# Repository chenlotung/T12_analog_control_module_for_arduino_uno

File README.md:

# T12_analog_control_module_for_arduino_uno

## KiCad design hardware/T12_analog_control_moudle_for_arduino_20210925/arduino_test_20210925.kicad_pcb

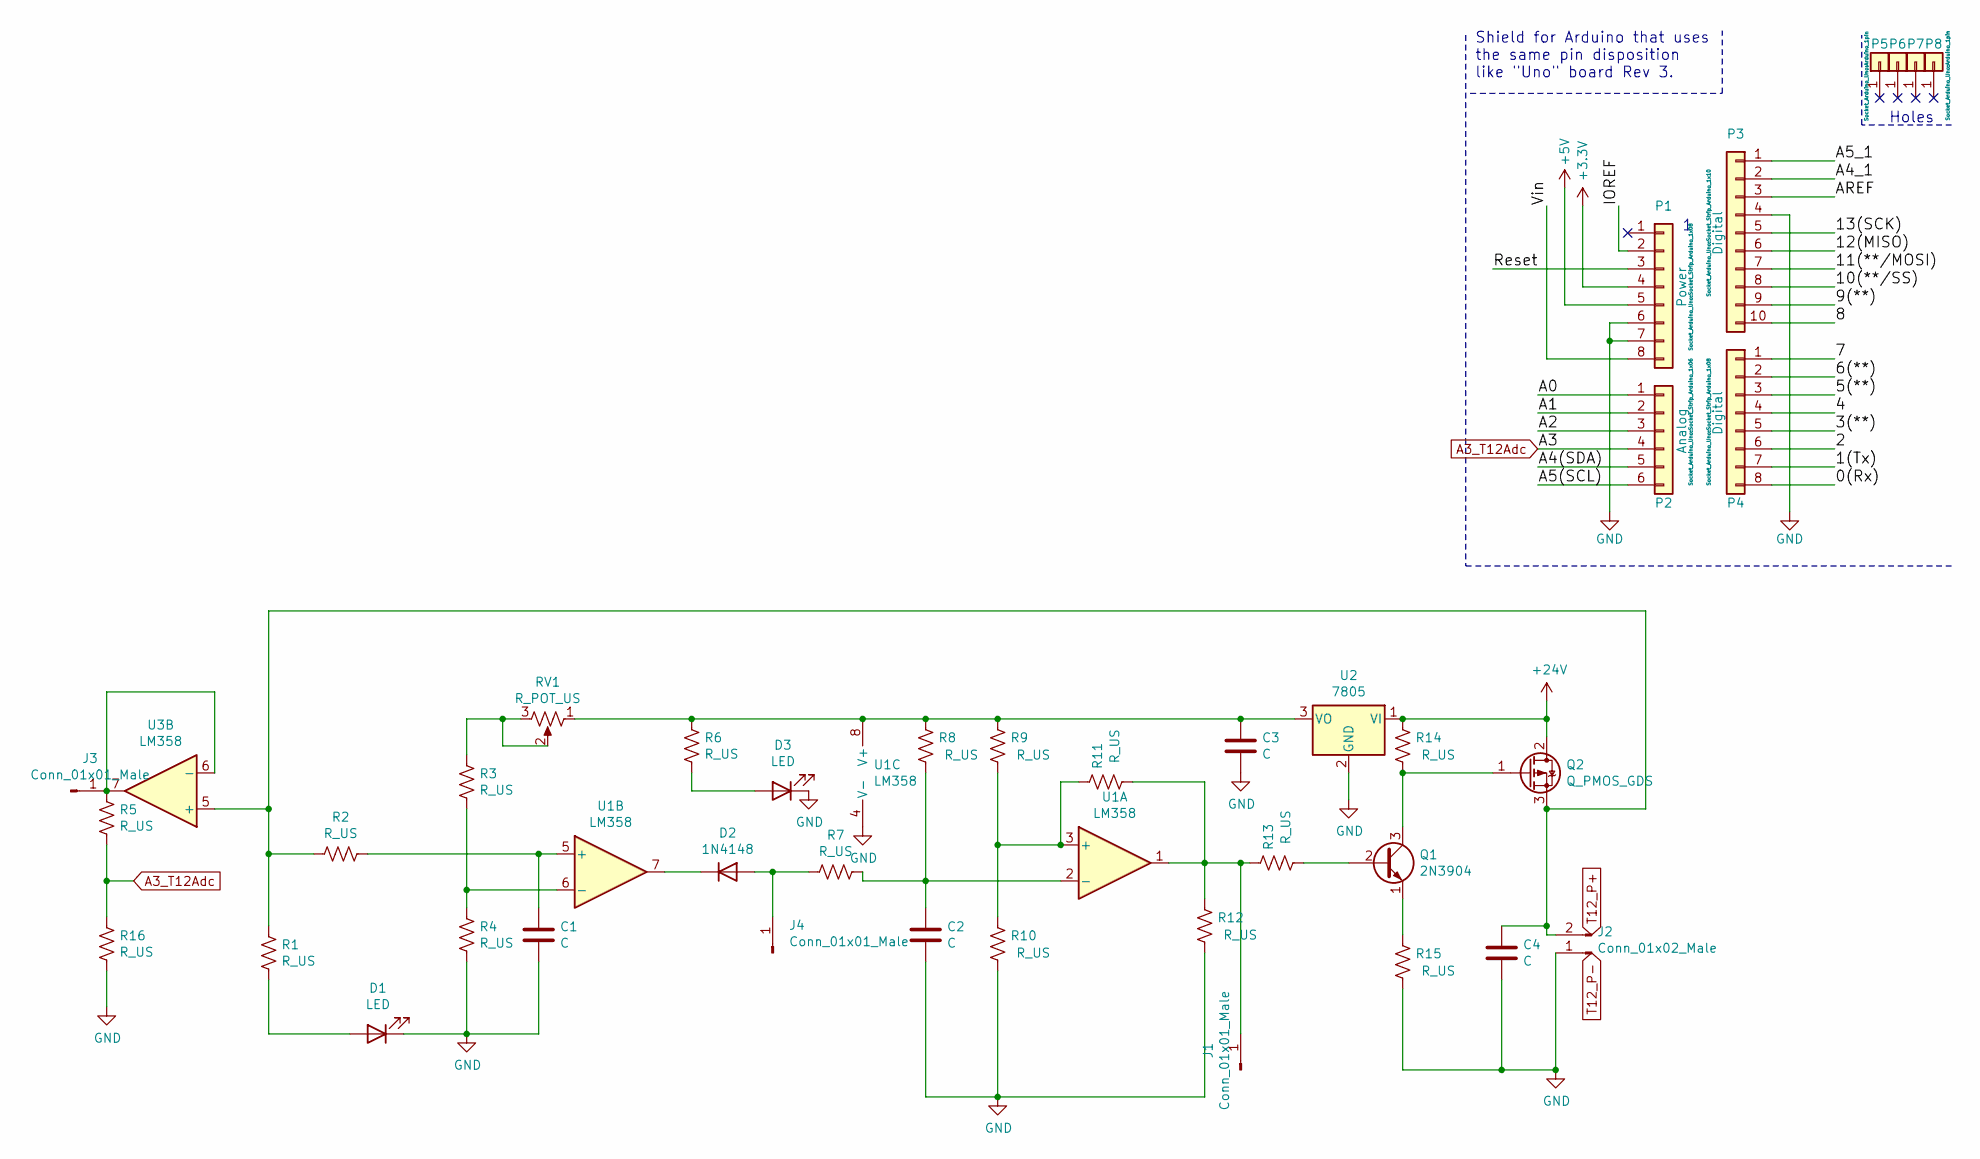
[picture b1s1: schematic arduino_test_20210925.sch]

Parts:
C1, C2, C3, C4: C; C_Disc_D6.0mm_W2.5mm_P5.00mm
D1, D3: LED; LED_D5.0mm
D2: 1N4148; D_DO-35_SOD27_P7.62mm_Horizontal
J1, J3, J4: Conn_01x01_Male; PinHeader_1x01_P2.54mm_Vertical
J2: Conn_01x02_Male; PinHeader_1x02_P2.54mm_Vertical
P1: Power; Socket_Strip_Arduino_1x08
P2: Analog; Socket_Strip_Arduino_1x06
P3: Digital; Socket_Strip_Arduino_1x10
P4: Digital; Socket_Strip_Arduino_1x08
P5, P6, P7, P8: CONN_01X01; Arduino_1pin
Q1: 2N3904; TO-92_Inline
Q2: Q_PMOS_GDS; TO-252-2
R1, R2, R3, R4, R5, R6, R7, R8, R9, R10, R11, R12, R13, R14, R15, R16: R_US; R_Axial_DIN0309_L9.0mm_D3.2mm_P2.54mm_Vertical
RV1: R_POT_US; Potentiometer_Alps_RK163_Single_Horizontal
U1, U3: LM358; DIP-8_W7.62mm_Socket_LongPads
U2: 7805; TO-220-3_Vertical

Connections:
+3V3: P1.4
+5V: P1.5
+24V: Q2.2 (D), R14.1, U2.1 (VI)
/0(Rx): P4.8
/1(Tx): P4.7
/2: P4.6
/3(**): P4.5
/4: P4.4
/5(**): P4.3
/6(**): P4.2
/7: P4.1
/8: P3.10
/9(**): P3.9
/10(**/SS): P3.8
/11(**/MOSI): P3.7
/12(MISO): P3.6
/13(SCK): P3.5
/A0: P2.1
/A1: P2.2
/A2: P2.3
/A4(SDA): P2.5
/A4_1: P3.2
/A5(SCL): P2.6
/A5_1: P3.1
/AREF: P3.3
/IOREF: P1.2
/Reset: P1.3
/Vin: P1.8
A3_T12Adc: P2.4, R5.2, R16.1
GND: C1.2, C2.2, C3.2, C4.2, D1.1 (K), D3.1 (K), J2.1, P1.6, P1.7, P3.4, R4.2, R10.2, R12.2, R15.2, R16.2, U1.4 (V-), U2.2 (GND)
unnamed: C1.1, R2.1, U1.5 (+)
unnamed: C2.1, R7.1, R8.2, U1.2 (-)
unnamed: C3.1, R6.1, R8.1, R9.1, RV1.1, U1.8 (V+), U2.3 (VO)
unnamed: C4.1, J2.2, Q2.3 (S), R1.1, R2.2, U3.5 (+)
unnamed: D1.2 (A), R1.2
unnamed: D2.1 (K), U1.7
unnamed: D2.2 (A), J4.1, R7.2
unnamed: D3.2 (A), R6.2
unnamed: J1.1, R11.2, R12.1, R13.1, U1.1
unnamed: J3.1, R5.1, U3.6 (-), U3.7
unnamed: Q1.1 (E), R15.1
unnamed: Q1.2 (B), R13.2
unnamed: Q1.3 (C), Q2.1 (G), R14.2
unnamed: R3.1, RV1.2, RV1.3
unnamed: R3.2, R4.1, U1.6 (-)
unnamed: R9.2, R10.1, R11.1, U1.3 (+)

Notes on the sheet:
Holes
Shield for Arduino that uses the same pin disposition like "Uno" board Rev 3.

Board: 2 copper layers, 41 parts (0 on the bottom side), 19 nets, no tracks yet.

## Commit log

2021-09-25 kicad init. V0.06222
